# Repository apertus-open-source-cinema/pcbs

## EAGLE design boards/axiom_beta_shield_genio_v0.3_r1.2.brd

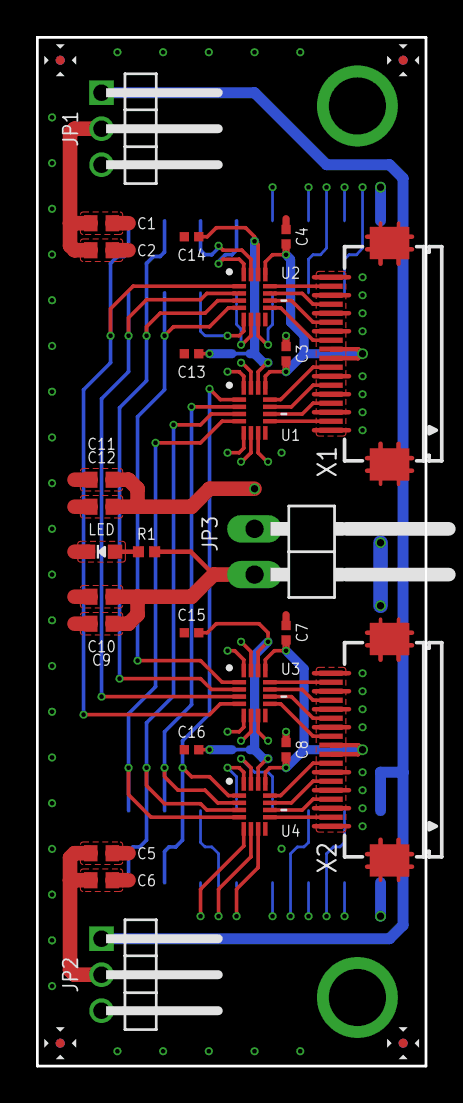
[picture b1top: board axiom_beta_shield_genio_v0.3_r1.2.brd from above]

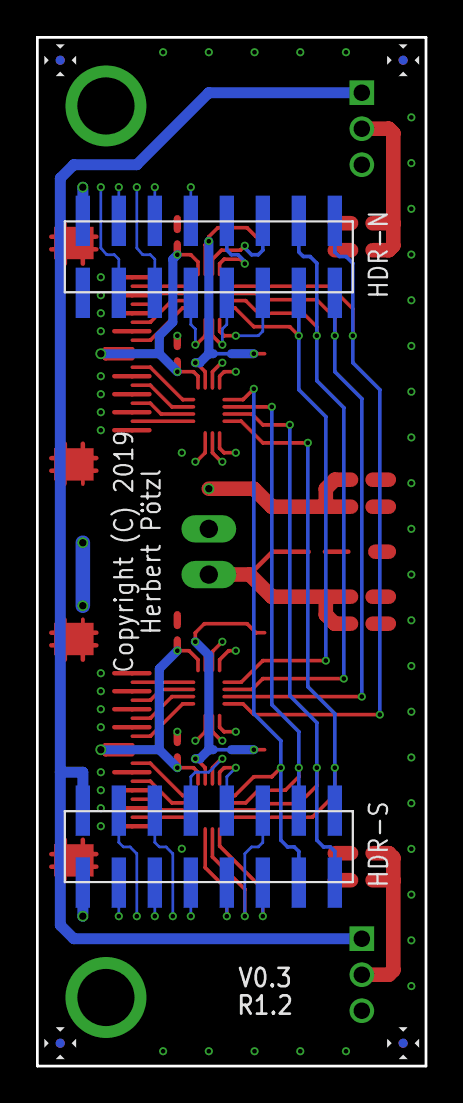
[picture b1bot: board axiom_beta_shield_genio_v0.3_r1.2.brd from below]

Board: 4 copper layers, 21.6 x 57.1 mm, 29 parts (2 on the bottom side), 51 nets.

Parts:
C1, C2, C5, C6, C9, C10, C11, C12: 0603-C
C3, C4, C7, C8, C13, C14, C15, C16: 0402-C
HDR-N: 2X08M_SMD
HDR-S: 2X08M_SMD
JP1, JP2: 1X03M/90-S
JP3: 1X02/90
LED: CHIPLED_0603_NOOUTLINE
R1: 10k; 0402-B
U1, U2, U3, U4: SN74AVC4T774RSV; QFN40P185X265X55-16N
X1, X2: FH12-18S-0.5SH

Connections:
0CH1: U1.9, X1.2
0CH2: U1.10, X1.4
0CH3: U1.11, X1.6
0CH4: U1.12, X1.8
0CH5: U2.9, X1.11
0CH6: U2.10, X1.13
0CH7: U2.11, X1.15
0CH8: U2.12, X1.17
0VCC: C1.1, C2.1, C3.1, C4.1, JP1.2, U1.13, U2.13, X1.9, X1.10
1CH1: U4.9, X2.2
1CH2: U4.10, X2.4
1CH3: U4.11, X2.6
1CH4: U4.12, X2.8
1CH5: U3.9, X2.11
1CH6: U3.10, X2.13
1CH7: U3.11, X2.15
1CH8: U3.12, X2.17
1VCC: C5.1, C6.1, C7.1, C8.1, JP2.2, U3.13, U4.13, X2.9, X2.10
3V3: HDR-S.2, JP1.1, JP2.1
GND: C1.2, C2.2, C3.2, C4.2, C5.2, C6.2, C7.2, C8.2, C9.2, C10.2, C11.2, C12.2, C13.2, C14.2, C15.2, C16.2, HDR-N.1, HDR-N.2, JP3.1, LED.C, U1.8, U2.8, U3.8, U4.8, X1.1, X1.3, X1.5, X1.7, X1.12, X1.14, X1.16, X1.18, X2.1, X2.3, X2.5, X2.7, X2.12, X2.14, X2.16, X2.18
unnamed: LED.A, R1.2
SH_N_IO0: HDR-N.12, U2.15
SH_N_IO1: HDR-N.11, U2.5
SH_N_IO2: HDR-N.10, U2.16
SH_N_IO3: HDR-N.9, U2.6
SH_N_IO4: HDR-N.8, U1.15
SH_N_IO5: HDR-N.7, U2.7
SH_N_IO6: HDR-N.6, U1.16
SH_N_IO7: HDR-N.5, U1.5
SH_N_IO8: HDR-N.4, U1.6
SH_N_IO9: HDR-N.3, U1.7
SH_S_IO0: HDR-S.12, U4.6
SH_S_IO1: HDR-S.11, U4.5
SH_S_IO2: HDR-S.10, U4.16
SH_S_IO3: HDR-S.9, U4.7
SH_S_IO4: HDR-S.8, U4.15
SH_S_IO5: HDR-S.7, U3.7
SH_S_IO6: HDR-S.6, U3.6
SH_S_IO7: HDR-S.5, U3.5
SH_S_IO8: HDR-S.4, U3.16
SH_S_IO9: HDR-S.3, U3.15
VCCIO: C11.1, C12.1, C13.1, C14.1, C15.1, C16.1, HDR-S.1, U1.14, U2.14, U3.14, U4.14
VIN: C9.1, C10.1, JP1.3, JP2.3, JP3.2, R1.1
XX1_N: HDR-N.14, U2.3, U3.2
XX1_P: HDR-N.16, U2.1, U3.4
XX2_N: HDR-N.13, U2.4, U3.1
XX2_P: HDR-N.15, U2.2, U3.3
XX3_N: HDR-S.15, U1.3, U4.3
XX3_P: HDR-S.13, U1.1, U4.1
XX4_N: HDR-S.16, U1.4, U4.4
XX4_P: HDR-S.14, U1.2, U4.2

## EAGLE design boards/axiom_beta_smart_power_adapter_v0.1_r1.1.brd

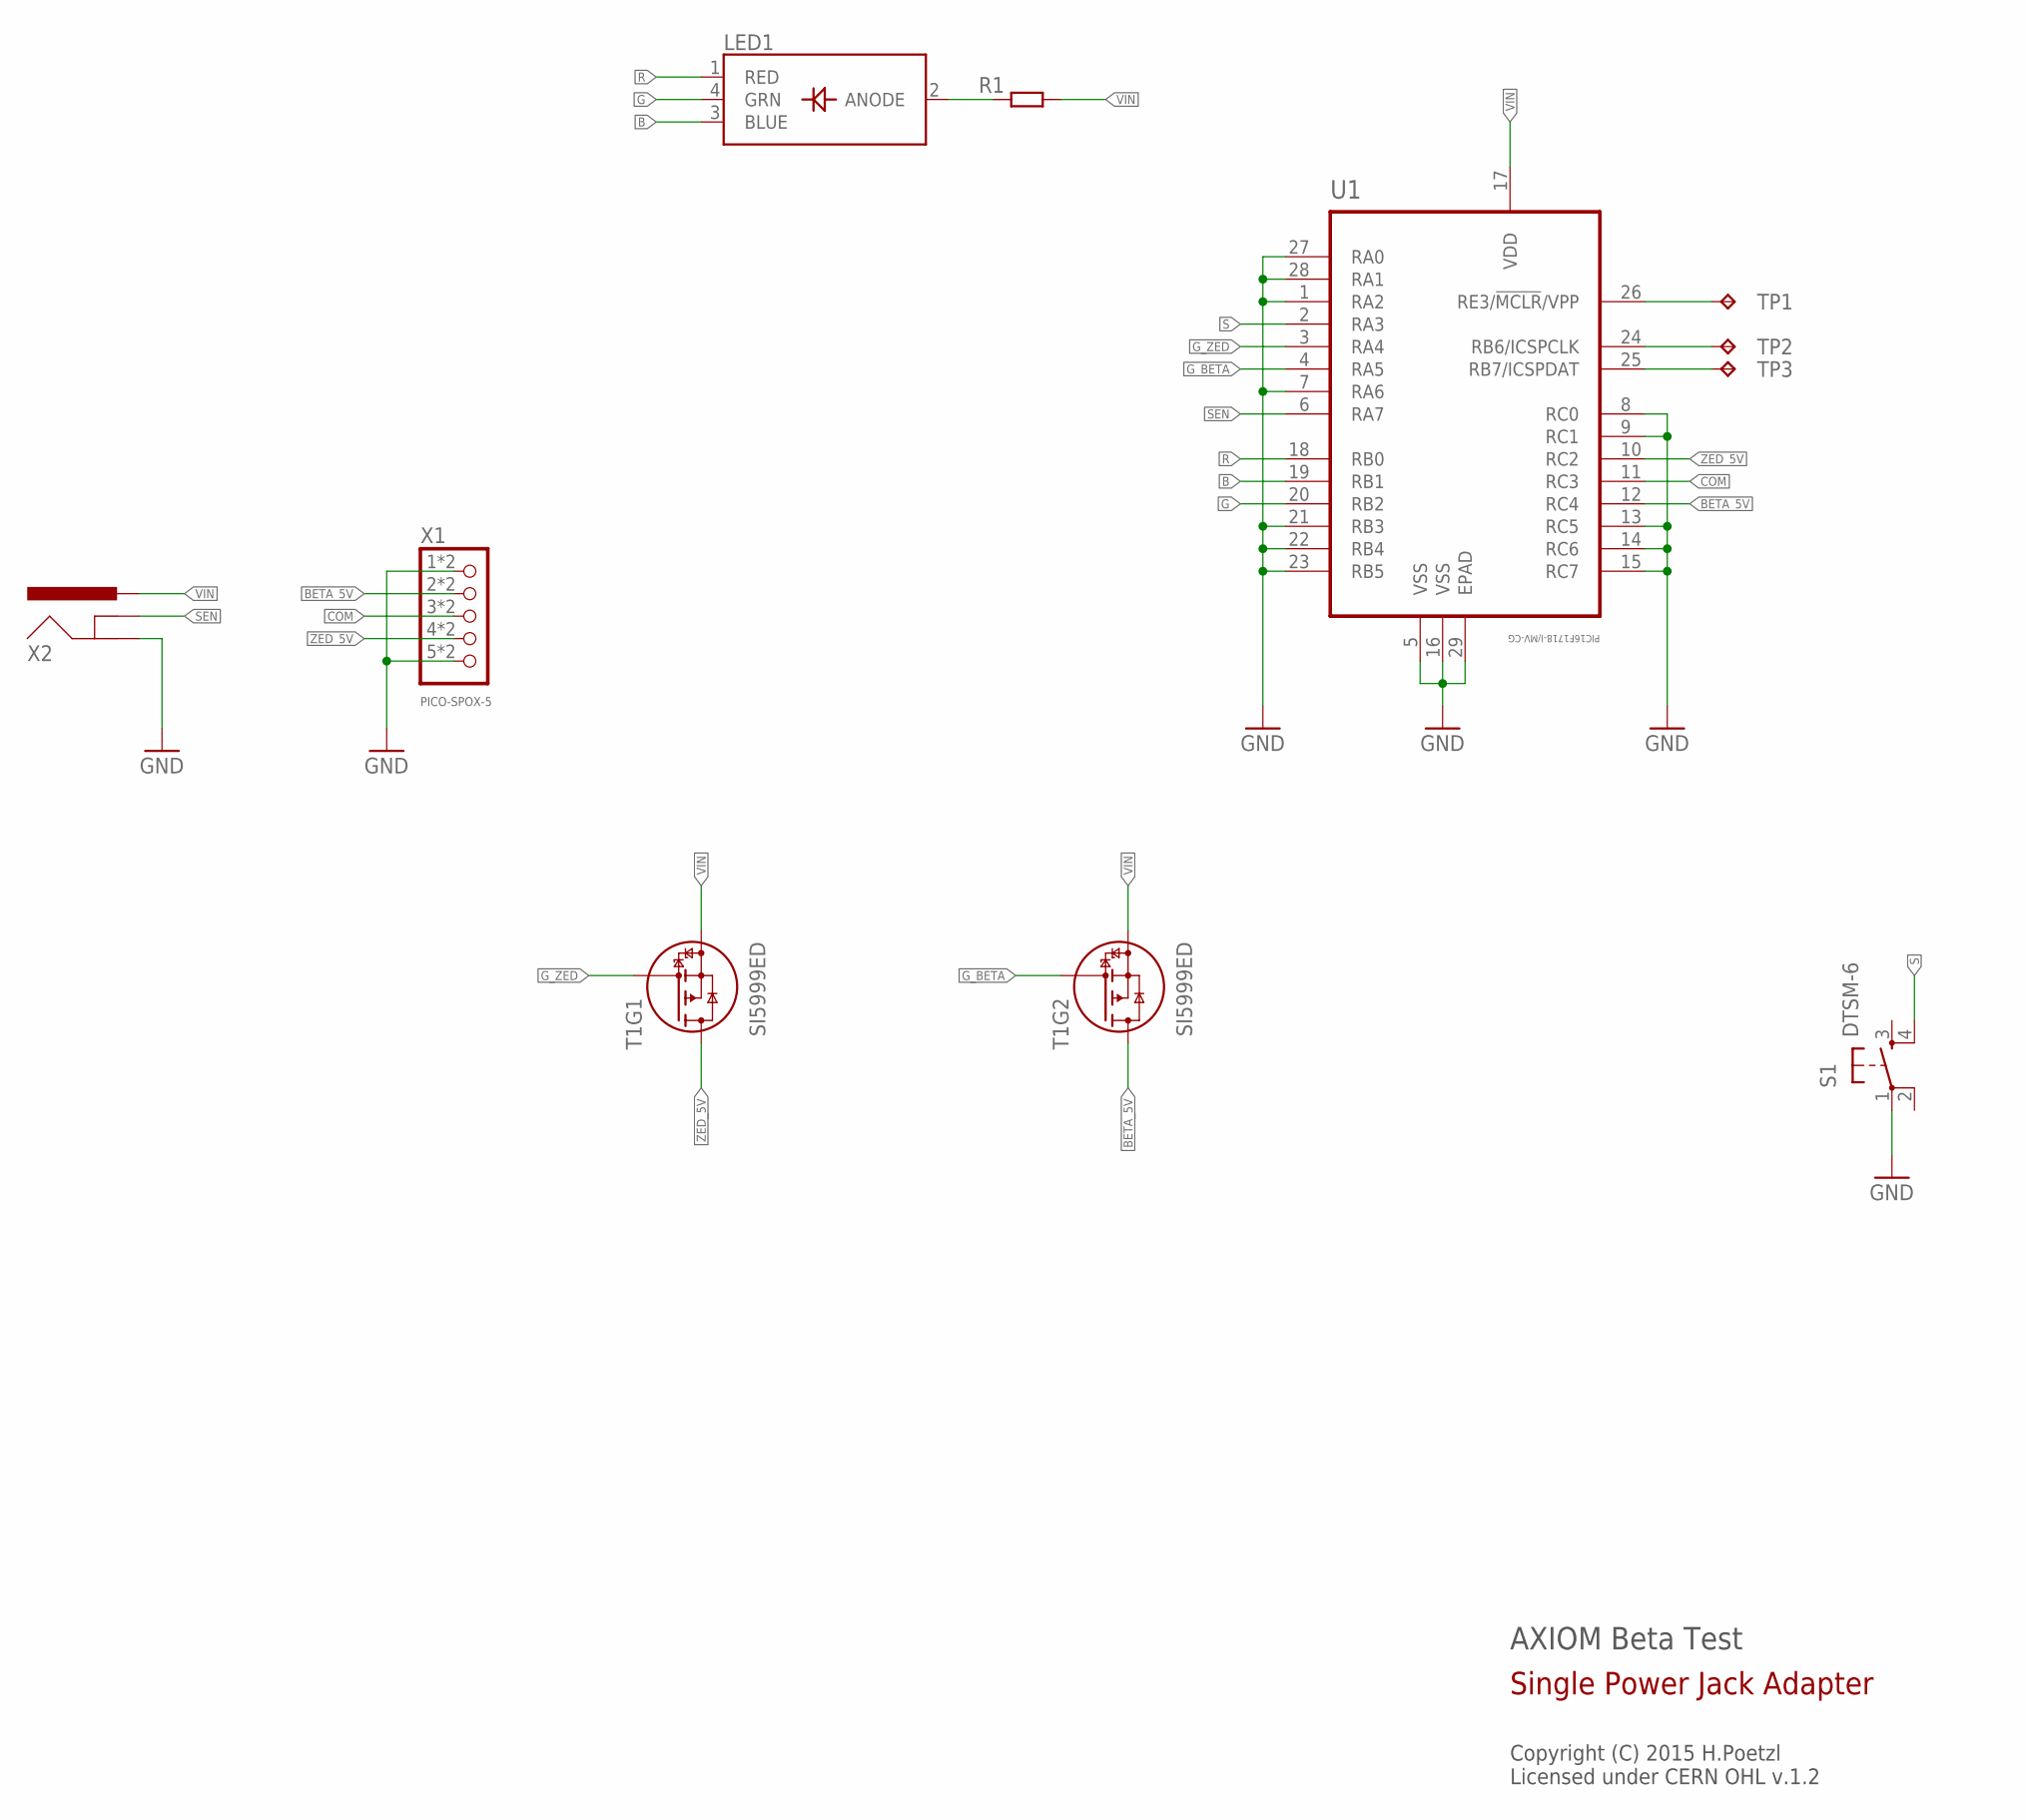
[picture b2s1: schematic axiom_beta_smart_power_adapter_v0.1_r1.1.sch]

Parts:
LED1: LED_RGB_PLCC4; RGBLED_PLCC4
R1: R0402-C; 0402-C
S1: DTSM-6; 3X4MM
T1: SI5999ED; PPAK-CHIPFET-DUAL
TP1, TP2, TP3: TPTP07R; TP07R
U1: PIC16F1718-I/MV-CG; QFN40P400X400X55-29N-CGND
X1: PICO-SPOX-5
X2: POWER_JACKPTH_SLOT; POWER_JACK_PTH_SLOT

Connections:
B: LED1.3 (BLUE), U1.19 (RB1)
BETA_5V: T1.5 (D), T1.6 (D), T1.EP56 (D), U1.12 (RC4), X1.2, X1.2A (2)
COM: U1.11 (RC3), X1.3, X1.3A (3)
G: LED1.4 (GRN), U1.20 (RB2)
GND: S1.1, U1.1 (RA2), U1.5 (VSS), U1.7 (RA6), U1.8 (RC0), U1.9 (RC1), U1.13 (RC5), U1.14 (RC6), U1.15 (RC7), U1.16 (VSS), U1.21 (RB3), U1.22 (RB4), U1.23 (RB5), U1.27 (RA0), U1.28 (RA1), U1.29 (EPAD), X1.1, X1.1A (1), X1.5, X1.5A (5), X2.GND
G_BETA: T1.4 (G), U1.4 (RA5)
G_ZED: T1.2 (G), U1.3 (RA4)
unnamed: LED1.2 (ANODE), R1.1
unnamed: TP1.TP, U1.26 (RE3/!MCLR!/VPP)
unnamed: TP2.TP, U1.24 (RB6/ICSPCLK)
unnamed: TP3.TP, U1.25 (RB7/ICSPDAT)
R: LED1.1 (RED), U1.18 (RB0)
S: S1.4, U1.2 (RA3)
SEN: U1.6 (RA7), X2.SHUNT (GNDBREAK)
VIN: R1.2, T1.1 (S), T1.3 (S), U1.17 (VDD), X2.PWR
ZED_5V: T1.7 (D), T1.8 (D), T1.EP78 (D), U1.10 (RC2), X1.4, X1.4A (4)

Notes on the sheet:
AXIOM Beta Test
Copyright (C) 2015 H.Poetzl Licensed under CERN OHL v.1.2
Single Power Jack Adapter

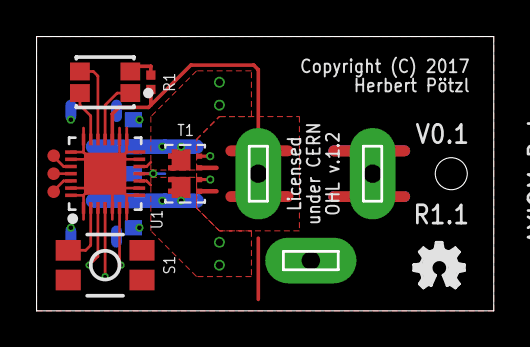
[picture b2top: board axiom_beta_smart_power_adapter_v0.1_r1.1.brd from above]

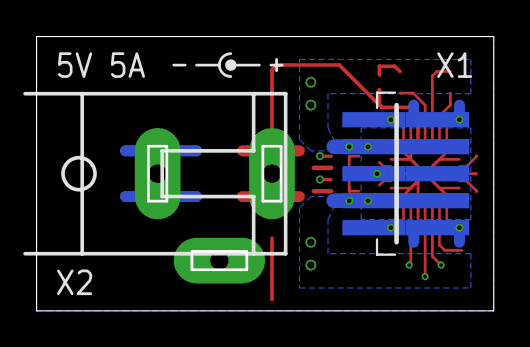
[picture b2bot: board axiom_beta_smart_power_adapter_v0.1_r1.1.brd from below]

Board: 4 copper layers, 25.4 x 15.2 mm, 11 parts (2 on the bottom side), 16 nets.

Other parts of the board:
LOGO1: OSHW_LOGO_FILLX0100-NT; OSHW_FILLX100_NOTEXT

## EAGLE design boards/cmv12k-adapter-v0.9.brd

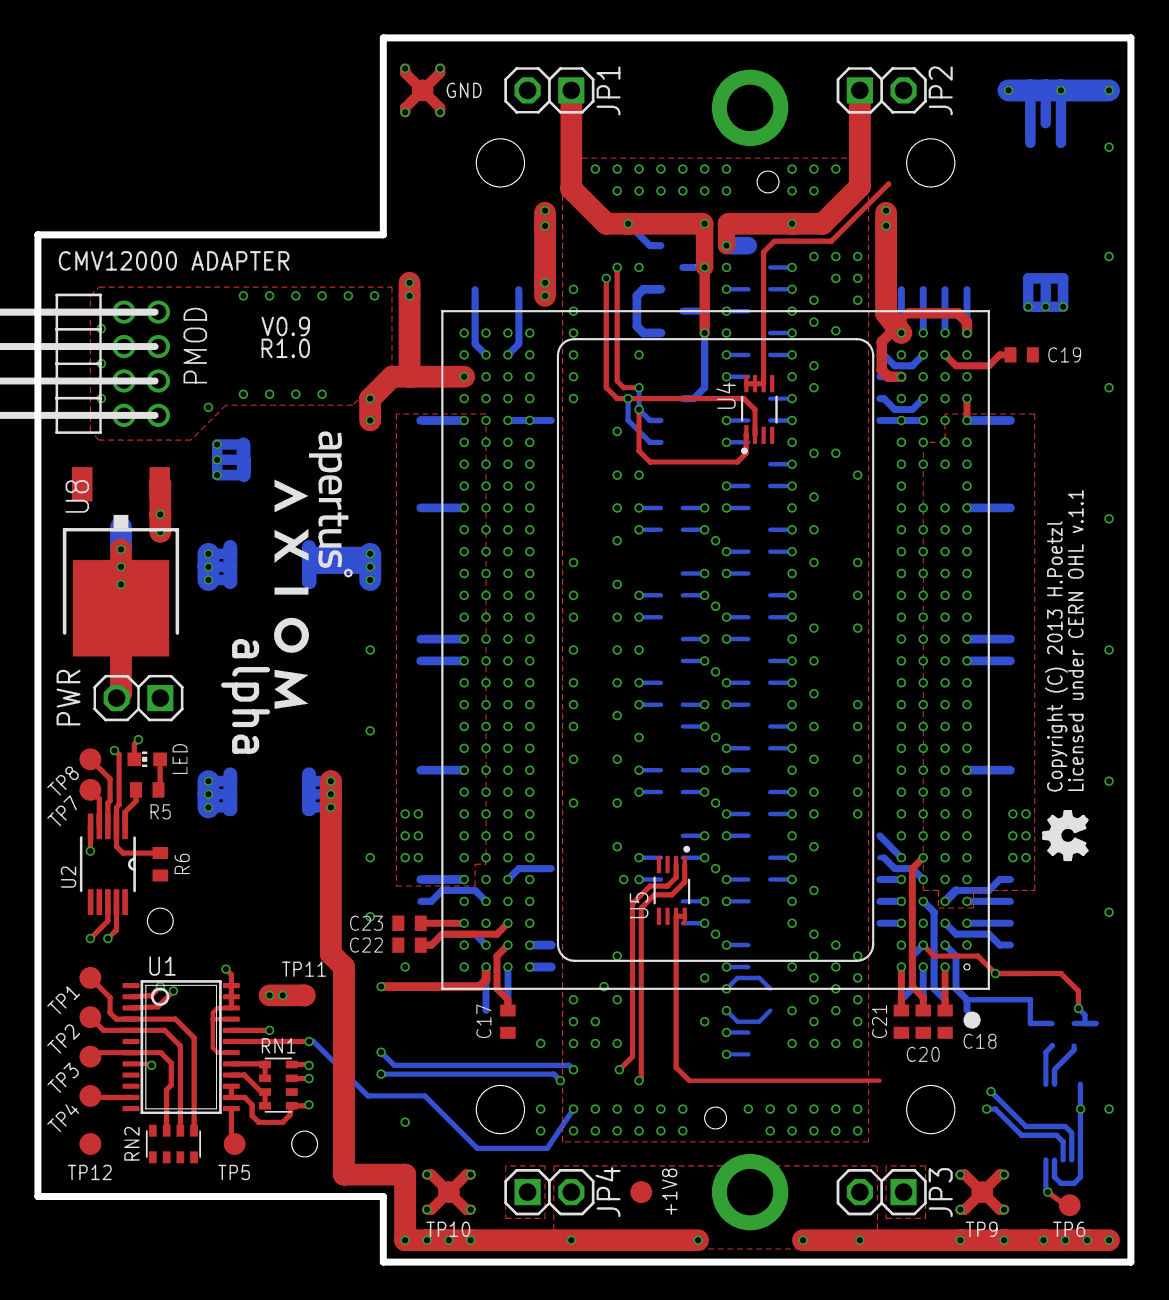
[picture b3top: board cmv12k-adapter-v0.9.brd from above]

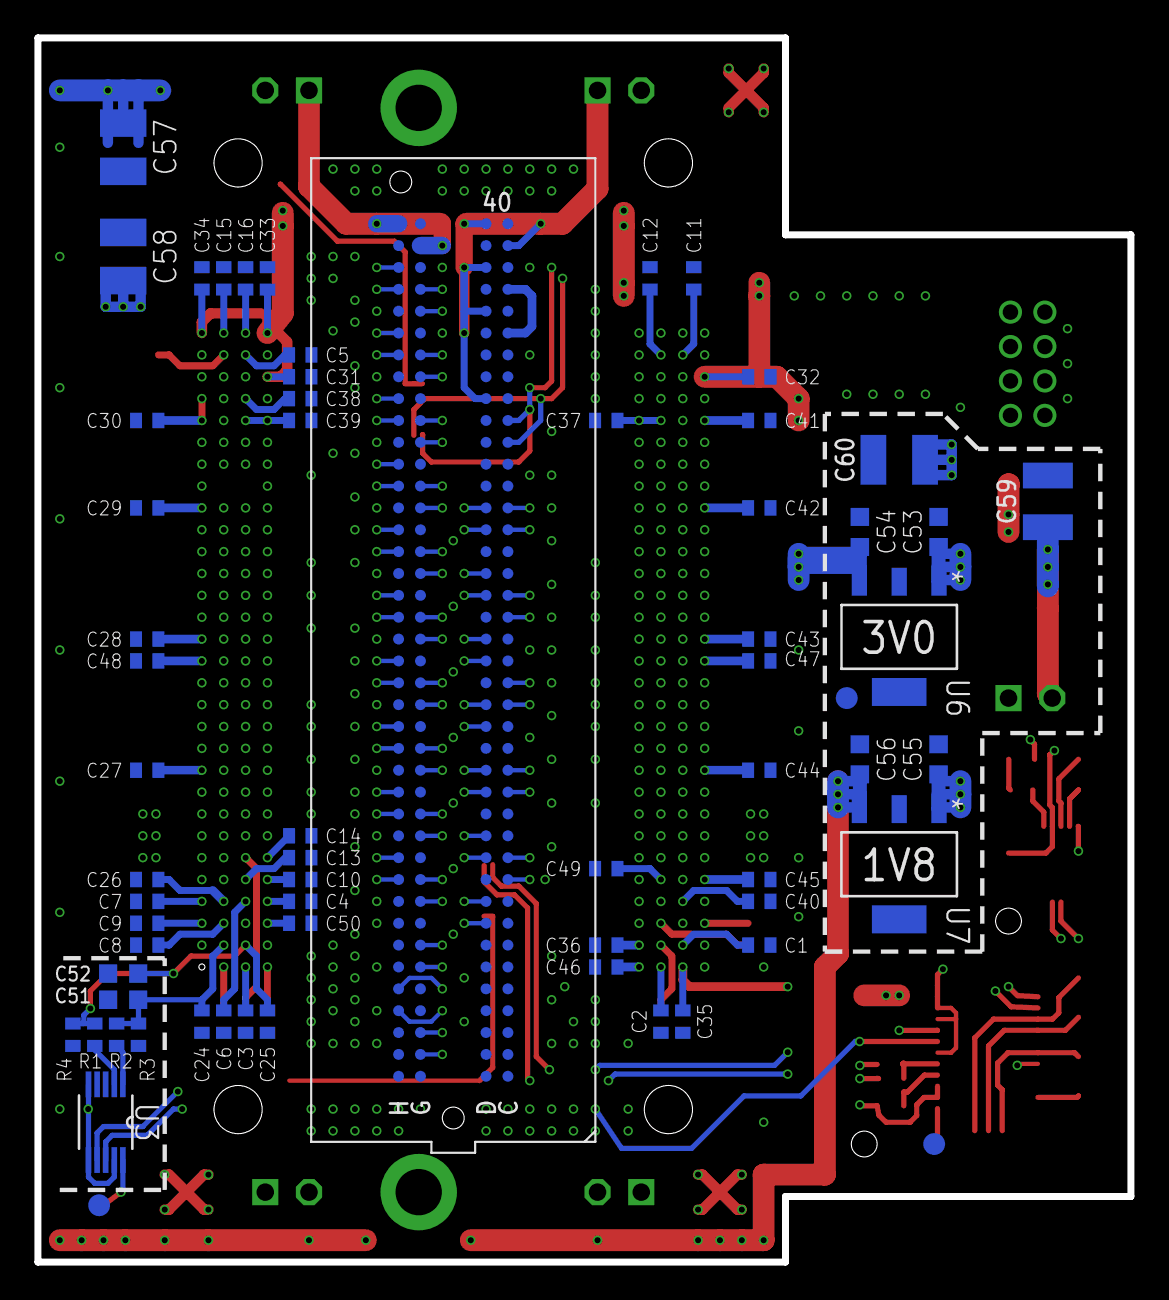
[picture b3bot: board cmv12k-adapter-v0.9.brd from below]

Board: 4 copper layers, 63.5 x 71.1 mm, 105 parts (63 on the bottom side), 130 nets.

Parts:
+1V8: TPB1,27; B1,27
C1, C2, C3, C4, C5, C6, C7, C8, C9, C10, C11, C12, C13, C14, C15, C16, C17, C18, C19, C20, C21, C22, C23, C24, C25, C26, C27, C28, C29, C30, C31, C32, C33, C34, C35, C36, C37, C38, C39, C40, C41, C42, C43, C44, C45, C46, C47, C48, C49, C50: 100n; C0402
C51, C52, C53, C54, C55, C56: 10u; C0603K
C57, C58: 100u; C1210
C59, C60: 100u; C1210K
GND: TPB1,27; B1,27
GND*1, GND*2, GND*3: TPB1,27; B1,27
JP1, JP2, JP3, JP4: 1X02-S
LED: RED; CHIP-LED0603
LOGO1: OSHW_LOGO_FILLX0100-NT; OSHW_FILLX100_NOTEXT
PMOD: PMOD-8; 2X04/90/2MM
PWR: 1X02-S
R1, R2: 1R; R0402
R3, R4: R0402
R5: 220R; R0402
R6: 10k; R0402
RN1, RN2: 10k; EXBV8V
TP1, TP2, TP3, TP4, TP5, TP6, TP7, TP8, TP9, TP10, TP11, TP12: TPB1,27; B1,27
U1: LM96080; TSSOP24
U2: PCA9537; TSSOP-10
U3: AD5647R; SOP50P490X110-10N
U4, U5: LM75BGD; SOT996-2/3
U6: MCP1826S-3002E/DB; SOT230P700X180-4N
U7: MCP1826S-1802E/DB; SOT230P700X180-4N
U8: AP1084TO252; TO252
U$1: CMV12000ANDON+LM; 10-30-07-237-400T4+LM
U$5: APERTUS_LOGO334X100; APERTUS_LOGO_334X100
U$13: AXIOM_LOGO525X80; AXIOM_LOGO_525X80
ZED1: FMC-LPC-ZED_NOCCZED; ASP-134604-01-ZED

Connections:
+1V8: +1V8.TP, C56.1, C57.1, JP2.2, JP3.2, JP4.2, U7.3
+1V8A: C26.1, C27.1, C28.1, C29.1, C30.1, C48.1, JP3.1, TP9.TP, U1.19, U$1.A10, U$1.A15, U$1.A16, U$1.A22, U$1.A26, U$1.A27, U$1.B4
+1V8B: C41.1, C42.1, C43.1, C44.1, C45.1, C46.1, C47.1, JP4.1, TP10.TP, U1.20, U$1.E1, U$1.H5, U$1.H10, U$1.H15, U$1.H16, U$1.H22, U$1.H26
+3V0: C31.1, C32.1, C33.1, C34.1, C35.1, C54.1, RN1.3, TP11.TP, U6.3, U$1.A30, U$1.D28, U$1.D30, U$1.G1, U$1.H28
+3V3: C17.1, C18.1, C19.1, C20.1, C21.1, C22.1, C23.1, C36.1, C37.1, C38.1, C39.1, C40.1, C49.1, C50.1, C53.1, C55.1, C58.1, C60.1, JP1.2, R6.1, RN1.2, RN2.2, RN2.3, RN2.4, TP12.TP, U1.1, U1.6, U1.9, U1.12, U2.6, U2.10, U3.5, U3.6, U3.9, U4.6, U4.7, U4.8, U5.7, U5.8, U6.1, U7.1, U8.2, U$1.C26, U$1.C27, U$1.D3, U$1.D26, U$1.E2, U$1.E26, U$1.F5, U$1.F26, U$1.G4
+5V: C59.1, PWR.2, U8.3
GND: C1.2, C2.2, C3.2, C4.2, C5.2, C6.2, C7.2, C8.2, C9.2, C10.2, C11.2, C12.2, C13.2, C14.2, C15.2, C16.2, C24.2, C25.2, C26.2, C27.2, C28.2, C29.2, C30.2, C31.2, C32.2, C33.2, C34.2, C35.2, C36.2, C37.2, C38.2, C39.2, C40.2, C41.2, C42.2, C43.2, C44.2, C45.2, C46.2, C47.2, C48.2, C49.2, C50.2, C51.2, C52.2, C53.2, C54.2, C55.2, C56.2, C57.2, C58.2, C59.2, C60.2, GND.TP, GND*1.TP, GND*2.TP, GND*3.TP, LED.C, PWR.1, R3.2, R4.2, RN1.1, RN1.4, U1.8, U1.14, U1.15, U1.18, U1.21, U1.22, U1.23, U1.24, U2.5, U3.3, U3.4, U4.4, U4.5, U5.4, U5.5, U5.6, U6.2, U6.4, U7.2, U7.4, U8.1, U$1.A9, U$1.A21, U$1.A25, U$1.A28, U$1.A29, U$1.B5, U$1.B22, U$1.B26, U$1.B27, U$1.B28, U$1.C15, U$1.C16, U$1.C28, U$1.D2, U$1.D25, U$1.D27, U$1.D29, U$1.E3, U$1.E15, U$1.E16, U$1.E25, U$1.E27, U$1.F27, U$1.G5, U$1.H1, U$1.H6, U$1.H9, U$1.H21, U$1.H25, U$1.H27, ZED1.C1, ZED1.C4, ZED1.C5, ZED1.C8, ZED1.C9, ZED1.C12, ZED1.C13, ZED1.C16, ZED1.C17, ZED1.C20, ZED1.C21, ZED1.C24, ZED1.C25, ZED1.C28, ZED1.C29, ZED1.C32, ZED1.C33, ZED1.C36, ZED1.C38, ZED1.C40, ZED1.D2, ZED1.D3, ZED1.D6, ZED1.D7, ZED1.D10, ZED1.D13, ZED1.D16, ZED1.D19, ZED1.D22, ZED1.D25, ZED1.D28, ZED1.D37, ZED1.D39, ZED1.G1, ZED1.G4, ZED1.G5, ZED1.G8, ZED1.G11, ZED1.G14, ZED1.G17, ZED1.G20, ZED1.G23, ZED1.G26, ZED1.G29, ZED1.G32, ZED1.G35, ZED1.G38, ZED1.G40, ZED1.H3, ZED1.H6, ZED1.H9, ZED1.H12, ZED1.H15, ZED1.H18, ZED1.H21, ZED1.H24, ZED1.H27, ZED1.H30, ZED1.H33, ZED1.H36, ZED1.H39
unnamed: C17.2, U$1.F2
unnamed: C18.2, U$1.B1
unnamed: C19.2, U$1.B29
unnamed: C20.2, U$1.C6
unnamed: C21.2, U$1.D1
unnamed: C22.2, U$1.F3
unnamed: C23.2, U$1.H3
unnamed: C1.1, U$1.G2
unnamed: C2.1, U$1.F1
unnamed: C3.1, U$1.C1
unnamed: C4.1, U$1.D4
unnamed: C5.1, U$1.C29
unnamed: C6.1, U$1.C4
unnamed: C7.1, U$1.A4
unnamed: C8.1, U$1.B3
unnamed: C9.1, U$1.A3
unnamed: C10.1, U$1.D5
unnamed: C11.1, U$1.G29
unnamed: C12.1, U$1.F29
unnamed: C13.1, U$1.C5
unnamed: C14.1, U$1.D6
unnamed: C15.1, U$1.B30
unnamed: C16.1, U$1.C30
unnamed: U$1.B6, ZED1.H11
unnamed: U$1.B7, ZED1.H10
unnamed: PMOD.1, U$1.F28
unnamed: U$1.D7, ZED1.D12
unnamed: U$1.D8, ZED1.D11
unnamed: PMOD.8, U$1.H29
unnamed: PMOD.2, U$1.E28
unnamed: PMOD.7, U$1.G28
unnamed: PMOD.10, U$1.E30
unnamed: PMOD.4, U$1.G30
unnamed: U$1.B8, ZED1.H14
unnamed: U$1.C9, ZED1.D15
unnamed: U$1.C10, ZED1.D14
unnamed: ZED1.C35, ZED1.C37
unnamed: JP1.1, ZED1.C39, ZED1.D32, ZED1.D36, ZED1.D38, ZED1.D40
unnamed: JP2.1, ZED1.G39, ZED1.H40
unnamed: R1.2, U3.2
unnamed: U$1.G10, ZED1.G13
unnamed: U$1.A11, ZED1.D18
unnamed: U$1.A12, ZED1.D17
unnamed: U$1.C11, ZED1.H17
unnamed: U$1.C12, ZED1.H16
unnamed: U$1.A13, ZED1.D21
unnamed: U$1.A14, ZED1.D20
unnamed: U$1.D13, ZED1.H20
unnamed: U$1.D14, ZED1.H19
unnamed: U$1.F16, ZED1.G22
unnamed: U$1.F17, ZED1.G21
unnamed: U$1.A17, ZED1.H26
unnamed: U$1.A18, ZED1.H25
unnamed: U$1.C17, ZED1.D24
unnamed: U$1.C18, ZED1.D23
unnamed: U$1.A19, ZED1.H29
unnamed: U$1.A20, ZED1.H28
unnamed: U$1.C19, ZED1.D27
unnamed: U$1.C20, ZED1.D26
unnamed: U$1.D21, ZED1.H32
unnamed: U$1.D22, ZED1.H31
unnamed: U$1.A23, ZED1.H35
unnamed: U$1.A24, ZED1.H34
unnamed: U$1.B24, ZED1.H38
unnamed: U$1.B25, ZED1.H37
unnamed: U$1.D15, ZED1.H23
unnamed: U$1.D16, ZED1.H22
unnamed: U$1.G22, ZED1.G34
unnamed: U$1.G23, ZED1.G33
unnamed: U$1.E22, ZED1.G30
unnamed: U$1.E21, ZED1.G31
unnamed: U$1.F21, ZED1.G27
unnamed: U$1.F20, ZED1.G28
unnamed: U$1.E20, ZED1.C26
unnamed: U$1.E19, ZED1.C27
unnamed: U$1.F19, ZED1.G24
unnamed: U$1.F18, ZED1.G25
unnamed: U$1.E18, ZED1.C22
unnamed: U$1.E17, ZED1.C23
unnamed: U$1.H23, ZED1.G37
unnamed: U$1.H24, ZED1.G36
unnamed: U$1.G15, ZED1.G18
unnamed: U$1.G14, ZED1.G19
unnamed: U$1.H14, ZED1.C18
unnamed: U$1.H13, ZED1.C19
unnamed: U$1.G13, ZED1.G15
unnamed: U$1.G12, ZED1.G16
unnamed: U$1.H12, ZED1.C14
unnamed: U$1.H11, ZED1.C15
unnamed: U$1.G11, ZED1.G12
unnamed: U$1.B9, ZED1.H13
unnamed: U$1.F9, ZED1.C10
unnamed: U$1.F8, ZED1.C11
unnamed: U$1.E8, ZED1.G9
unnamed: U$1.E7, ZED1.G10
unnamed: U$1.F7, ZED1.G6
unnamed: U$1.F6, ZED1.G7
unnamed: U$1.E5, ZED1.H5
unnamed: U$1.E6, ZED1.H4
unnamed: U$1.G6, ZED1.G3
unnamed: U$1.G7, ZED1.G2
unnamed: U$1.A5, ZED1.D9
unnamed: U$1.A6, ZED1.D8
unnamed: PMOD.9, U$1.H30
unnamed: PMOD.3, U$1.E29
unnamed: RN2.5, TP1.TP, U1.4
unnamed: R6.2, U2.2, U$1.F30
unnamed: R5.1, U2.1
unnamed: RN2.6, TP2.TP, U1.5
unnamed: TP8.TP, U2.3
unnamed: TP7.TP, U2.4
unnamed: RN1.5, RN1.6, U1.17
unnamed: RN2.7, TP3.TP, U1.7
unnamed: TP4.TP, U1.11
unnamed: TP5.TP, U1.13
unnamed: RN1.7, RN1.8, U1.16
unnamed: R2.2, U3.1
unnamed: LED.A, R5.2
unnamed: TP6.TP, U3.10
SCL: U1.3, U2.8, U3.7, U4.2, U5.2, ZED1.C30
SDA: U1.2, U2.9, U3.8, U4.1, U5.1, ZED1.C31
VTREF: C24.1, C51.1, R2.1, R3.1, U$1.B2
VTSIG: C25.1, C52.1, R1.1, R4.1, U$1.C2

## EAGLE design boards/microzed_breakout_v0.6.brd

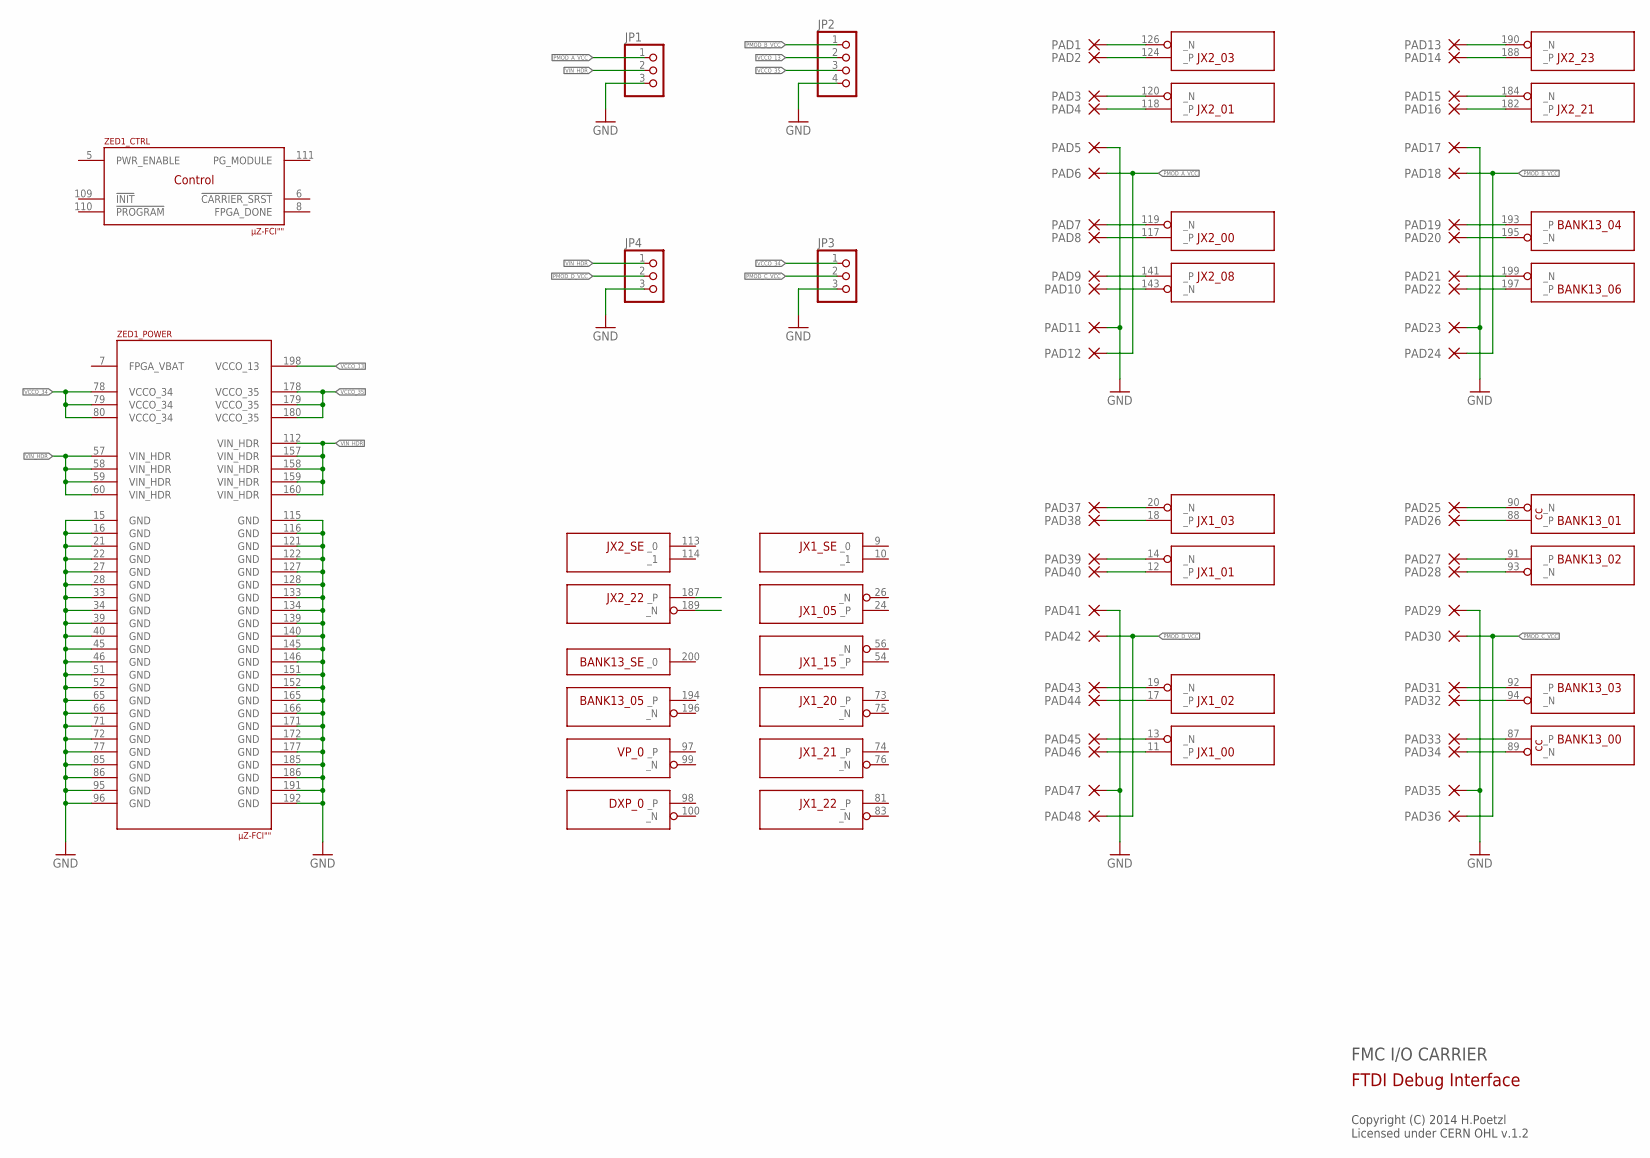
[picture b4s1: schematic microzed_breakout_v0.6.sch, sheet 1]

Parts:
JP1, JP3, JP4: PINHD-1X03_2.54; 1X03
JP2: PINHD-1X04_2.54; 1X04
PAD1, PAD2, PAD3, PAD4, PAD5, PAD6, PAD7, PAD8, PAD9, PAD10, PAD11, PAD12, PAD13, PAD14, PAD15, PAD16, PAD17, PAD18, PAD19, PAD20, PAD21, PAD22, PAD23, PAD24, PAD25, PAD26, PAD27, PAD28, PAD29, PAD30, PAD31, PAD32, PAD33, PAD34, PAD35, PAD36, PAD37, PAD38, PAD39, PAD40, PAD41, PAD42, PAD43, PAD44, PAD45, PAD46, PAD47, PAD48: SMD-PAD1.6X3.8MM-U; 1.6X3.8U-MM
ZED1: µZ-FCI""; µZ

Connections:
BANK13_00_N: PAD34.1, ZED1.89 (_N)
BANK13_00_P: PAD33.1, ZED1.87 (_P)
BANK13_01_N: PAD25.1, ZED1.90 (_N)
BANK13_01_P: PAD26.1, ZED1.88 (_P)
BANK13_02_N: PAD28.1, ZED1.93 (_N)
BANK13_02_P: PAD27.1, ZED1.91 (_P)
BANK13_03_N: PAD32.1, ZED1.94 (_N)
BANK13_03_P: PAD31.1, ZED1.92 (_P)
BANK13_04_N: PAD20.1, ZED1.195 (_N)
BANK13_04_P: PAD19.1, ZED1.193 (_P)
BANK13_06_N: PAD21.1, ZED1.199 (_N)
BANK13_06_P: PAD22.1, ZED1.197 (_P)
FPGA_VBAT: ZED1.7 (FPGA_VBAT)
GND: JP1.3, JP2.4, JP3.3, JP4.3, PAD5.1, PAD11.1, PAD17.1, PAD23.1, PAD29.1, PAD35.1, PAD41.1, PAD47.1, ZED1.15 (GND), ZED1.16 (GND), ZED1.21 (GND), ZED1.22 (GND), ZED1.27 (GND), ZED1.28 (GND), ZED1.33 (GND), ZED1.34 (GND), ZED1.39 (GND), ZED1.40 (GND), ZED1.45 (GND), ZED1.46 (GND), ZED1.51 (GND), ZED1.52 (GND), ZED1.65 (GND), ZED1.66 (GND), ZED1.71 (GND), ZED1.72 (GND), ZED1.77 (GND), ZED1.85 (GND), ZED1.86 (GND), ZED1.95 (GND), ZED1.96 (GND), ZED1.115 (GND), ZED1.116 (GND), ZED1.121 (GND), ZED1.122 (GND), ZED1.127 (GND), ZED1.128 (GND), ZED1.133 (GND), ZED1.134 (GND), ZED1.139 (GND), ZED1.140 (GND), ZED1.145 (GND), ZED1.146 (GND), ZED1.151 (GND), ZED1.152 (GND), ZED1.165 (GND), ZED1.166 (GND), ZED1.171 (GND), ZED1.172 (GND), ZED1.177 (GND), ZED1.185 (GND), ZED1.186 (GND), ZED1.191 (GND), ZED1.192 (GND); also elsewhere on the board
JX1_00_N: PAD45.1, ZED1.13 (_N)
JX1_00_P: PAD46.1, ZED1.11 (_P)
JX1_01_N: PAD39.1, ZED1.14 (_N)
JX1_01_P: PAD40.1, ZED1.12 (_P)
JX1_02_N: PAD43.1, ZED1.19 (_N)
JX1_02_P: PAD44.1, ZED1.17 (_P)
JX1_03_N: PAD37.1, ZED1.20 (_N)
JX1_03_P: PAD38.1, ZED1.18 (_P)
JX2_00_N: PAD7.1, ZED1.119 (_N)
JX2_00_P: PAD8.1, ZED1.117 (_P)
JX2_01_N: PAD3.1, ZED1.120 (_N)
JX2_01_P: PAD4.1, ZED1.118 (_P)
JX2_03_N: PAD1.1, ZED1.126 (_N)
JX2_03_P: PAD2.1, ZED1.124 (_P)
JX2_08_N: PAD10.1, ZED1.143 (_N)
JX2_08_P: PAD9.1, ZED1.141 (_P)
JX2_21_N: PAD15.1, ZED1.184 (_N)
JX2_21_P: PAD16.1, ZED1.182 (_P)
JX2_23_N: PAD13.1, ZED1.190 (_N)
JX2_23_P: PAD14.1, ZED1.188 (_P)
PMOD_A_VCC: JP1.1, PAD6.1, PAD12.1
PMOD_B_VCC: JP2.1, PAD18.1, PAD24.1
PMOD_C_VCC: JP3.2, PAD30.1, PAD36.1
PMOD_D_VCC: JP4.2, PAD42.1, PAD48.1
VCCO_13: JP2.2, ZED1.198 (VCCO_13)
VCCO_34: JP3.1, ZED1.78 (VCCO_34), ZED1.79 (VCCO_34), ZED1.80 (VCCO_34)
VCCO_35: JP2.3, ZED1.178 (VCCO_35), ZED1.179 (VCCO_35), ZED1.180 (VCCO_35)
VIN_HDR: JP1.2, JP4.1, ZED1.57 (VIN_HDR), ZED1.58 (VIN_HDR), ZED1.59 (VIN_HDR), ZED1.60 (VIN_HDR), ZED1.112 (VIN_HDR), ZED1.157 (VIN_HDR), ZED1.158 (VIN_HDR), ZED1.159 (VIN_HDR), ZED1.160 (VIN_HDR)

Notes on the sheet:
FMC I/O CARRIER
Copyright (C) 2014 H.Poetzl Licensed under CERN OHL v.1.2
FTDI Debug Interface

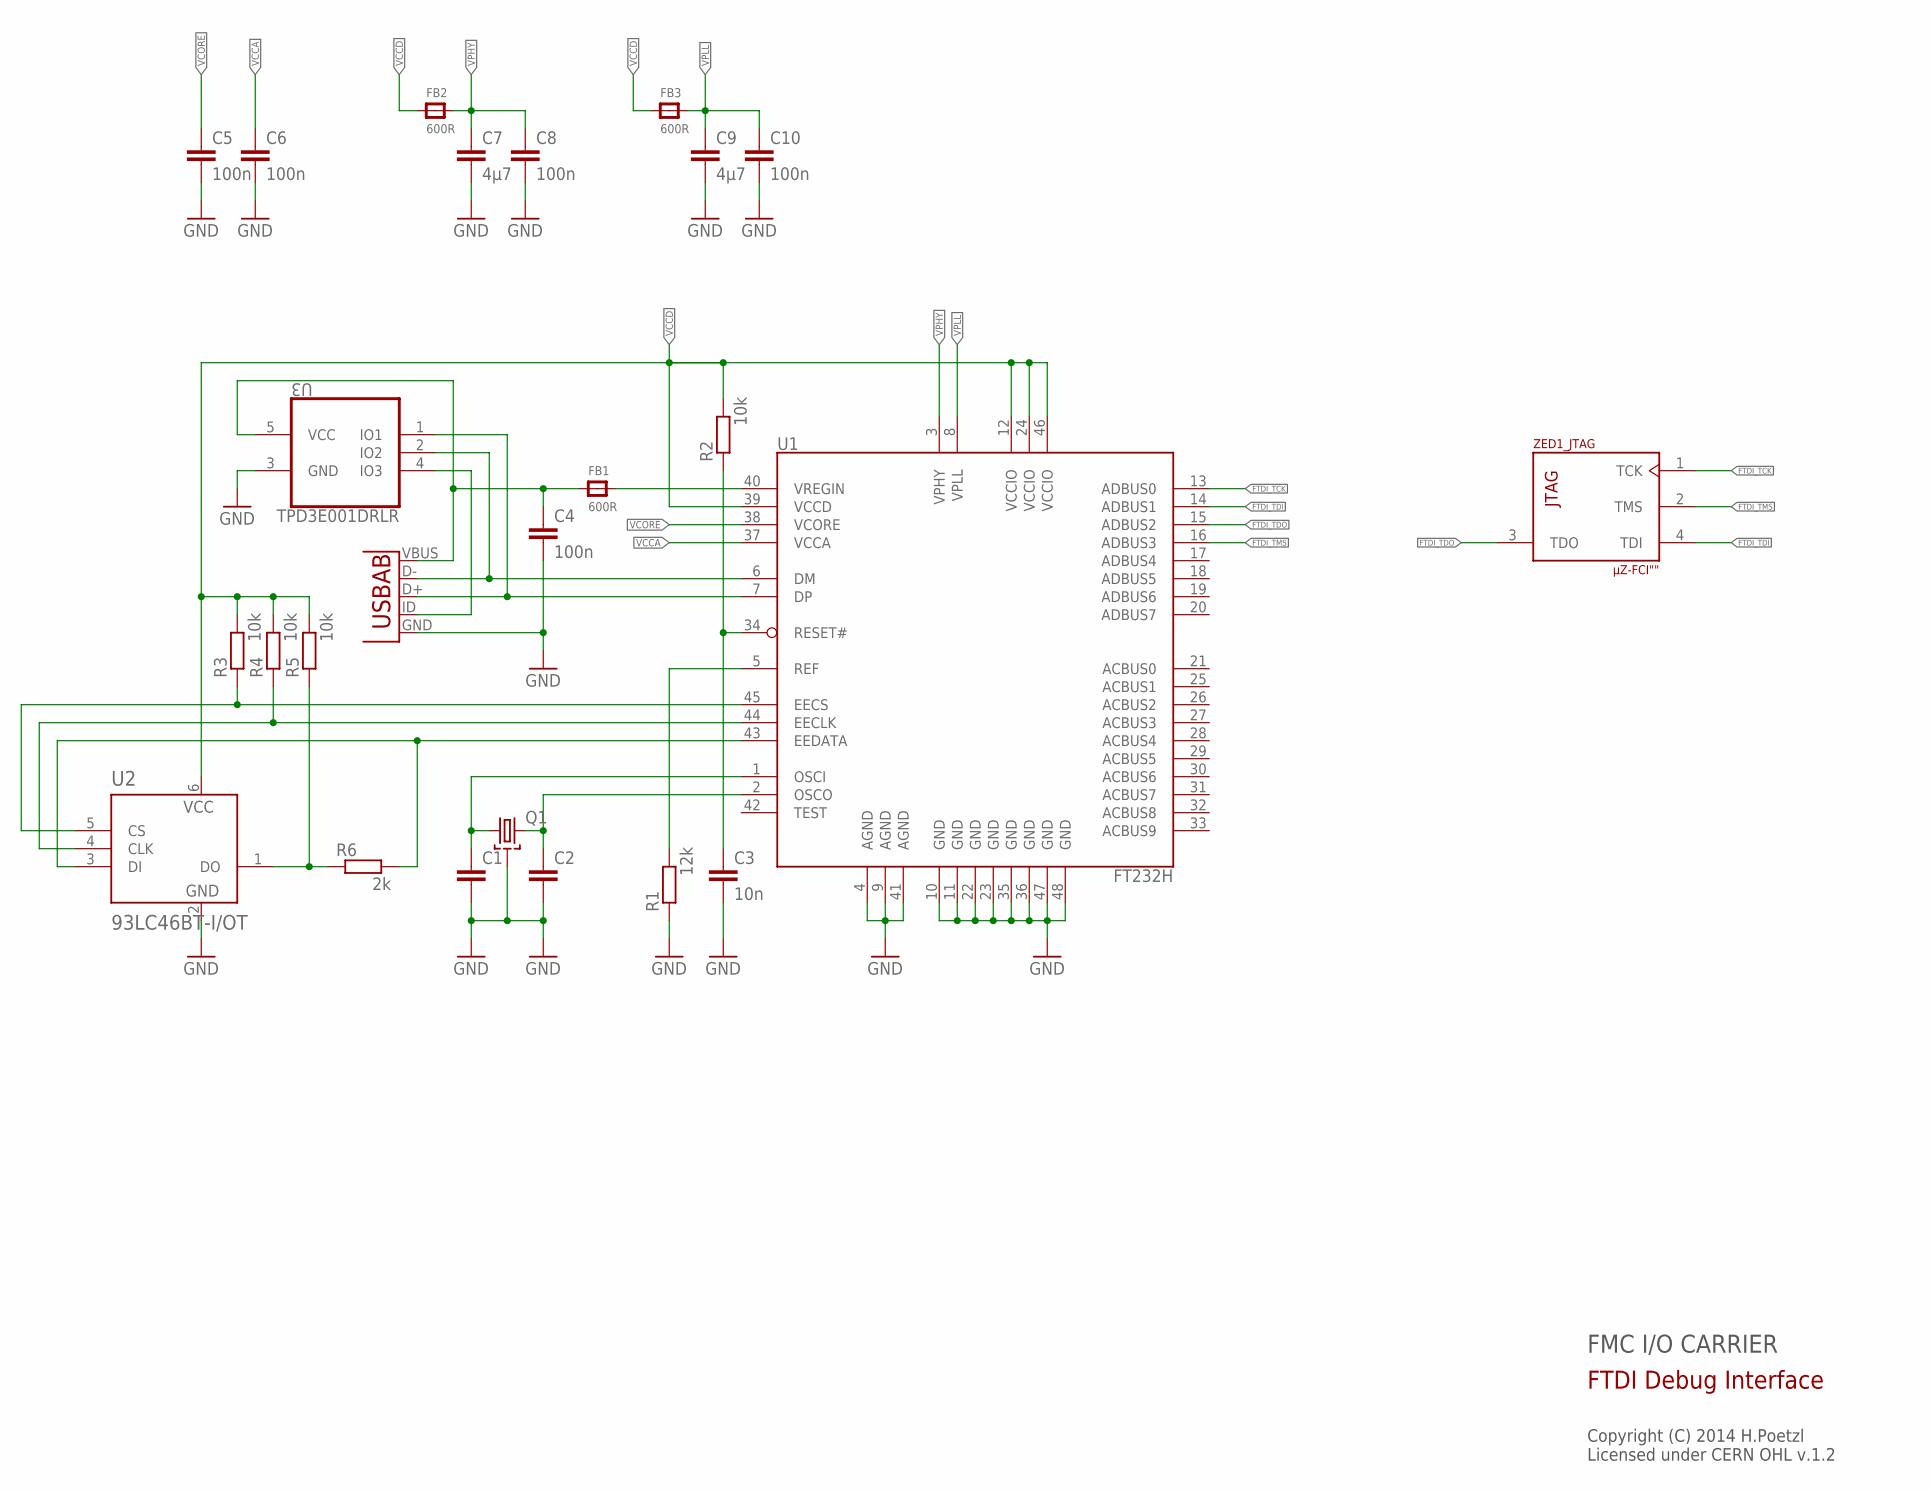
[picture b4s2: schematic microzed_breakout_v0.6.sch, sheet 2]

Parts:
C1, C2: C-EUC0402K; C0402K
C3: 10n; C0402K
C4, C5, C6, C8, C10: 100n; C0402K
C7, C9: 4µ7; C0402K
FB1, FB2, FB3: 600R; _0603MP
Q1: SMD-4P-2G-3.2X2.5; ABM8G
R1: 12k; R0402
R2, R3, R4, R5: 10k; R0402
R6: 2k; R0402
U1: FT232H; LQFP48
U2: 93LC46BT-I/OT; SOT95P280X145-6N
U3: TPD3E001DRLR; SOT50P160X60-5N
USB: USB-AB; USB-AB-MICRO-SMD
ZED1: µZ-FCI""; µZ

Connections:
EE_CLK1: R4.1, U1.44 (EECLK), U2.4 (CLK)
EE_CS1: R3.1, U1.45 (EECS), U2.5 (CS)
EE_DATA1: R6.2, U1.43 (EEDATA), U2.3 (DI)
FPGA_VBAT: ZED1.7 (FPGA_VBAT)
FTDI_D+: U1.7 (DP), U3.1 (IO1), USB.D+
FTDI_D-: U1.6 (DM), U3.2 (IO2), USB.D-
FTDI_TCK: U1.13 (ADBUS0), ZED1.1 (TCK)
FTDI_TDI: U1.14 (ADBUS1), ZED1.4 (TDI)
FTDI_TDO: U1.15 (ADBUS2), ZED1.3 (TDO)
FTDI_TMS: U1.16 (ADBUS3), ZED1.2 (TMS)
GND: C1.2, C2.2, C3.2, C4.2, C5.2, C6.2, C7.2, C8.2, C9.2, C10.2, Q1.2 (GND), Q1.4 (GND), R1.1, U1.4 (AGND), U1.9 (AGND), U1.10 (GND), U1.11 (GND), U1.22 (GND), U1.23 (GND), U1.35 (GND), U1.36 (GND), U1.41 (AGND), U1.47 (GND), U1.48 (GND), U2.2 (VSS), U3.3 (GND), USB.GND; also elsewhere on the board
unnamed: R5.1, R6.1, U2.1 (DO)
unnamed: C1.1, Q1.1, U1.1 (OSCI)
unnamed: C2.1, Q1.3 (2), U1.2 (OSCO)
unnamed: C3.1, R2.1, U1.34 (RESET#)
unnamed: R1.2, U1.5 (REF)
unnamed: U3.4 (IO3), USB.ID (USBID)
VBUS: C4.1, FB1.1, U3.5 (VCC), USB.VBUS
VCCA: C6.1, U1.37 (VCCA)
VCCD: FB2.1, FB3.1, R2.2, R3.2, R4.2, R5.2, U1.12 (VCCIO), U1.24 (VCCIO), U1.39 (VCCD), U1.46 (VCCIO), U2.6 (VCC)
VCORE: C5.1, U1.38 (VCORE)
VPHY: C7.1, C8.1, FB2.2, U1.3 (VPHY)
VPLL: C9.1, C10.1, FB3.2, U1.8 (VPLL)
VREGIN: FB1.2, U1.40 (VREGIN)

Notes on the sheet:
FMC I/O CARRIER
Copyright (C) 2014 H.Poetzl Licensed under CERN OHL v.1.2
FTDI Debug Interface

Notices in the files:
boards/axiom_beta_shield_genio_v0.3_r1.2.brd:
Copyright (C) 2019
boards/axiom_beta_smart_power_adapter_v0.1_r1.1.brd:
Copyright (C) 2017
boards/cmv12k-adapter-v0.9.brd:
Copyright (C) 2013 H.Poetzl
Licensed under CERN OHL v.1.1
parts and their libraries:
microbuilder: This work is placed in the public domain, and may be freely used for commercial and non-commercial work with the following conditions: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
SparkFun-Connectors: Licensing: CC v3.0 Share-Alike You are welcome to use this library for commercial purposes.
